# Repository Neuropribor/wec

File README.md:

# wec
An open-source Wireless Electrophysological Complex

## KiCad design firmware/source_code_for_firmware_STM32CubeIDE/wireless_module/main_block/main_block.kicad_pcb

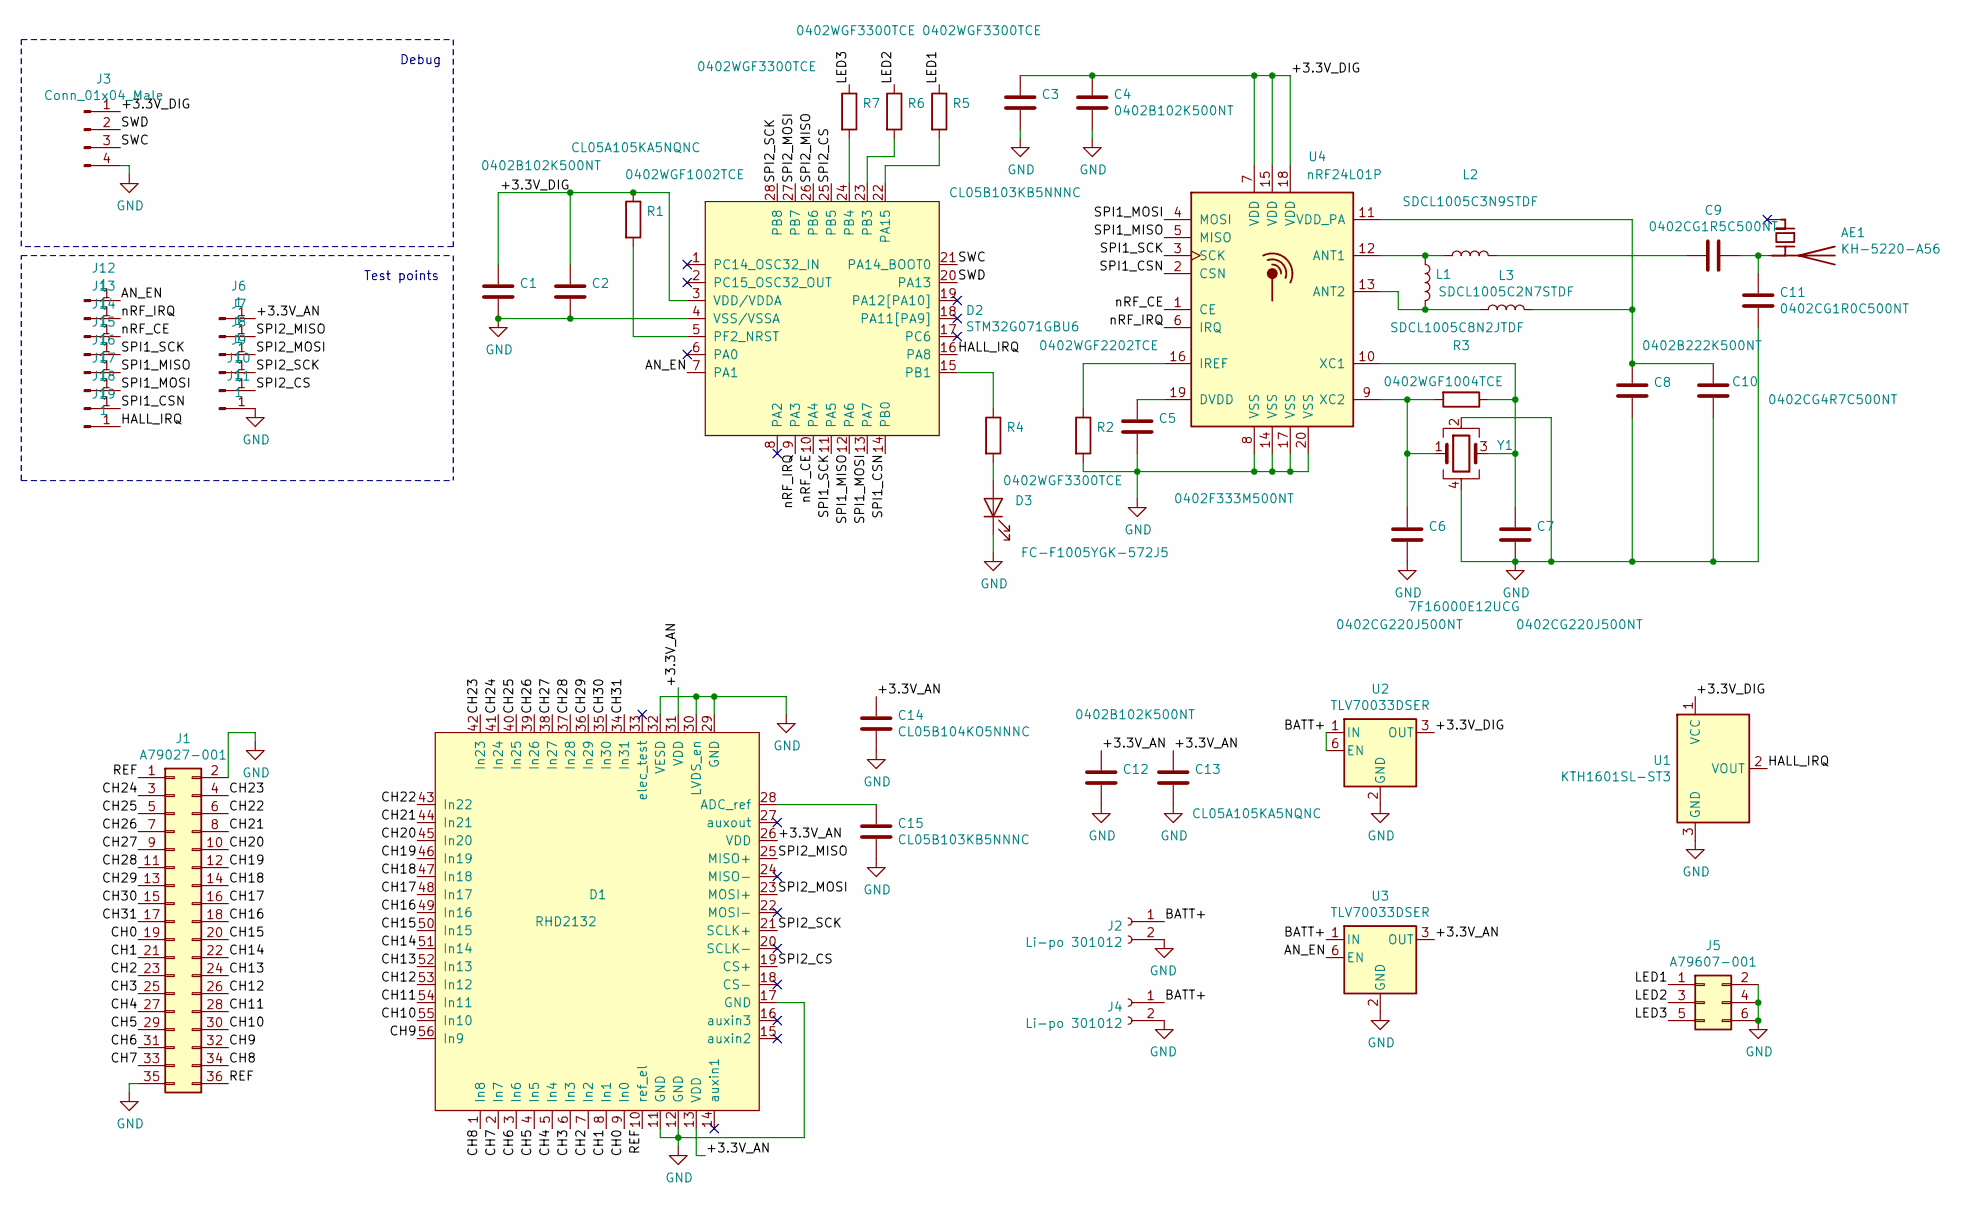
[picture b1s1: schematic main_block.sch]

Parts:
AE1: KH-5220-A56; R_2010_5025Metric_Pad1.52x2.65mm_HandSolder; LCSC C504003
C1, C4, C12: 0402B102K500NT; C_0402_1005Metric; LCSC C1523
C2, C13: CL05A105KA5NQNC; C_0402_1005Metric; LCSC C52923
C3, C15: CL05B103KB5NNNC; C_0402_1005Metric; LCSC C15195
C5: 0402F333M500NT; C_0402_1005Metric; LCSC C1585
C6, C7: 0402CG220J500NT; C_0402_1005Metric; LCSC C1555
C8: 0402B222K500NT; C_0402_1005Metric; LCSC C1531
C9: 0402CG1R5C500NT; C_0402_1005Metric; LCSC C1552
C10: 0402CG4R7C500NT; C_0402_1005Metric; LCSC C1569
C11: 0402CG1R0C500NT; C_0402_1005Metric; LCSC C1550
C14: CL05B104KO5NNNC; C_0402_1005Metric; LCSC C1525
D1: RHD2132; QFN-56-1EP_8x8mm_P0.5mm_EP4.5x5.2mm
D2: STM32G071GBU6; QFN50P400X400X60-28N; LCSC C529347
D3: FC-F1005YGK-572J5; LED_0402_1005Metric; LCSC C130722
J1: A79027-001
J2, J4: Li-po 301012; PinHeader_1x02_P2.00mm_Vertical
J3: Conn_01x04_Male; debug
J5: A79607-001
J6, J7, J8, J9, J10, J11, J12, J13, J14, J15, J16, J17, J18, J19: 1; debug_
L1: SDCL1005C8N2JTDF; L_0402_1005Metric; LCSC C16208
L2: SDCL1005C3N9STDF; L_0402_1005Metric; LCSC C14033
L3: SDCL1005C2N7STDF; L_0402_1005Metric; LCSC C27123
R1: 0402WGF1002TCE; R_0402_1005Metric; LCSC C25744
R2: 0402WGF2202TCE; R_0402_1005Metric; LCSC C25768
R3: 0402WGF1004TCE; R_0402_1005Metric; LCSC C26083
R4, R5, R6, R7: 0402WGF3300TCE; R_0402_1005Metric; LCSC C25104
U1: KTH1601SL-ST3; SOT-23; LCSC C516265
U2, U3: TLV70033DSER; WSON-6_1.5x1.5mm_P0.5mm; LCSC C97256
U4: nRF24L01P; QFN-20-1EP_4x4mm_P0.5mm_EP2.5x2.5mm; LCSC C8791
Y1: 7F16000E12UCG; Crystal_SMD_2016-4Pin_2.0x1.6mm; LCSC C252270

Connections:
/+3.3V_AN: C12.1, C13.1, C14.1, D1.13 (VDD), D1.26 (VDD), D1.31 (VDD), J6.1, U3.3 (OUT)
/+3.3V_DIG: C1.1, C2.1, C3.1, C4.1, D2.3 (VDD/VDDA), J3.1, R1.1, U1.1 (VCC), U2.3 (OUT), U4.7 (VDD), U4.15 (VDD), U4.18 (VDD)
/AN_EN: D2.7 (PA1), J12.1, U3.6 (EN)
/BATT+: J2.1, J4.1, U2.1 (IN), U2.6 (EN), U3.1 (IN)
/CH0: D1.9 (In0), J1.19
/CH1: D1.8 (In1), J1.21
/CH2: D1.7 (In2), J1.23
/CH3: D1.6 (In3), J1.25
/CH4: D1.5 (In4), J1.27
/CH5: D1.4 (In5), J1.29
/CH6: D1.3 (In6), J1.31
/CH7: D1.2 (In7), J1.33
/CH8: D1.1 (In8), J1.34
/CH9: D1.56 (In9), J1.32
/CH10: D1.55 (In10), J1.30
/CH11: D1.54 (In11), J1.28
/CH12: D1.53 (In12), J1.26
/CH13: D1.52 (In13), J1.24
/CH14: D1.51 (In14), J1.22
/CH15: D1.50 (In15), J1.20
/CH16: D1.49 (In16), J1.18
/CH17: D1.48 (In17), J1.16
/CH18: D1.47 (In18), J1.14
/CH19: D1.46 (In19), J1.12
/CH20: D1.45 (In20), J1.10
/CH21: D1.44 (In21), J1.8
/CH22: D1.43 (In22), J1.6
/CH23: D1.42 (In23), J1.4
/CH24: D1.41 (In24), J1.3
/CH25: D1.40 (In25), J1.5
/CH26: D1.39 (In26), J1.7
/CH27: D1.38 (In27), J1.9
/CH28: D1.37 (In28), J1.11
/CH29: D1.36 (In29), J1.13
/CH30: D1.35 (In30), J1.15
/CH31: D1.34 (In31), J1.17
/HALL_IRQ: D2.16 (PA8), J19.1, U1.2 (VOUT)
/LED1: J5.1, R5.1
/LED2: J5.3, R6.1
/LED3: J5.5, R7.1
/REF: D1.10 (ref_el), J1.1, J1.36
/SPI1_CSN: D2.14 (PB0), J18.1, U4.2 (CSN)
/SPI1_MISO: D2.12 (PA6), J16.1, U4.5 (MISO)
/SPI1_MOSI: D2.13 (PA7), J17.1, U4.4 (MOSI)
/SPI1_SCK: D2.11 (PA5), J15.1, U4.3 (SCK)
/SPI2_CS: D1.19 (CS+), D2.25 (PB5), J10.1
/SPI2_MISO: D1.25 (MISO+), D2.26 (PB6), J7.1
/SPI2_MOSI: D1.23 (MOSI+), D2.27 (PB7), J8.1
/SPI2_SCK: D1.21 (SCLK+), D2.28 (PB8), J9.1
/SWC: D2.21 (PA14_BOOT0), J3.3
/SWD: D2.20 (PA13), J3.2
/nRF_CE: D2.10 (PA4), J14.1, U4.1 (CE)
/nRF_IRQ: D2.9 (PA3), J13.1, U4.6 (IRQ)
GND: C1.2, C2.2, C3.2, C4.2, C5.2, C6.2, C7.2, C8.2, C10.2, C11.2, C12.2, C13.2, C14.2, C15.2, D1.11 (GND), D1.12 (GND), D1.17 (GND), D1.29 (GND), D1.30 (LVDS_en), D1.32 (VESD), D2.4 (VSS/VSSA), D3.1 (K), J1.2, J1.35, J2.2, J3.4, J4.2, J5.2, J5.4, J5.6, J11.1, R2.2, U1.3 (GND), U2.2 (GND), U3.2 (GND), U4.8 (VSS), U4.14 (VSS), U4.17 (VSS), U4.20 (VSS), Y1.2, Y1.4
unnamed: AE1.2 (PCB_Trace), C9.1, C11.1
unnamed: C5.1, U4.19 (DVDD)
unnamed: C6.1, R3.2, U4.9 (XC2), Y1.1
unnamed: C7.1, R3.1, U4.10 (XC1), Y1.3
unnamed: C9.2, L2.2
unnamed: C8.1, C10.1, L3.2, U4.11 (VDD_PA)
unnamed: C15.1, D1.28 (ADC_ref)
unnamed: D2.5 (PF2_NRST), R1.2
unnamed: D2.15 (PB1), R4.1
unnamed: D2.22 (PA15), R5.2
unnamed: D2.23 (PB3), R6.2
unnamed: D2.24 (PB4), R7.2
unnamed: D3.2 (A), R4.2
unnamed: L1.1, L2.1, U4.12 (ANT1)
unnamed: L1.2, L3.1, U4.13 (ANT2)
unnamed: R2.1, U4.16 (IREF)

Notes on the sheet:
Test points
Debug

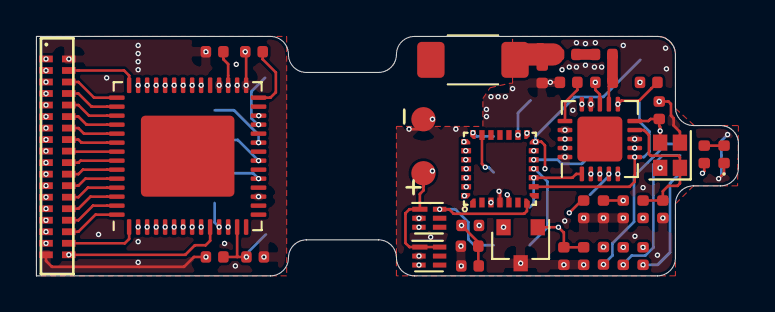
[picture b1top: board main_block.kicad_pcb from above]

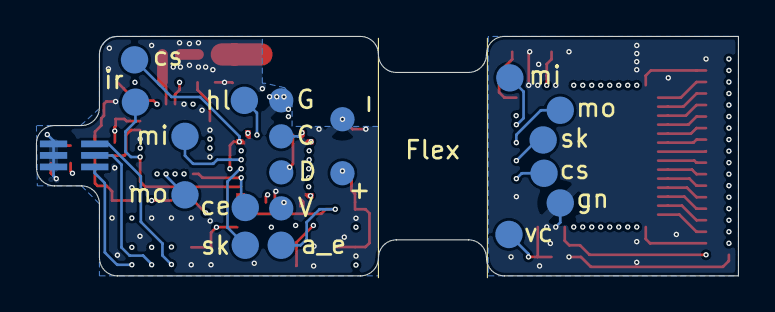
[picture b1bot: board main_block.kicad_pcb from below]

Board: 4 copper layers, 39.0 x 13.3 mm, 53 parts (17 on the bottom side), 70 nets.

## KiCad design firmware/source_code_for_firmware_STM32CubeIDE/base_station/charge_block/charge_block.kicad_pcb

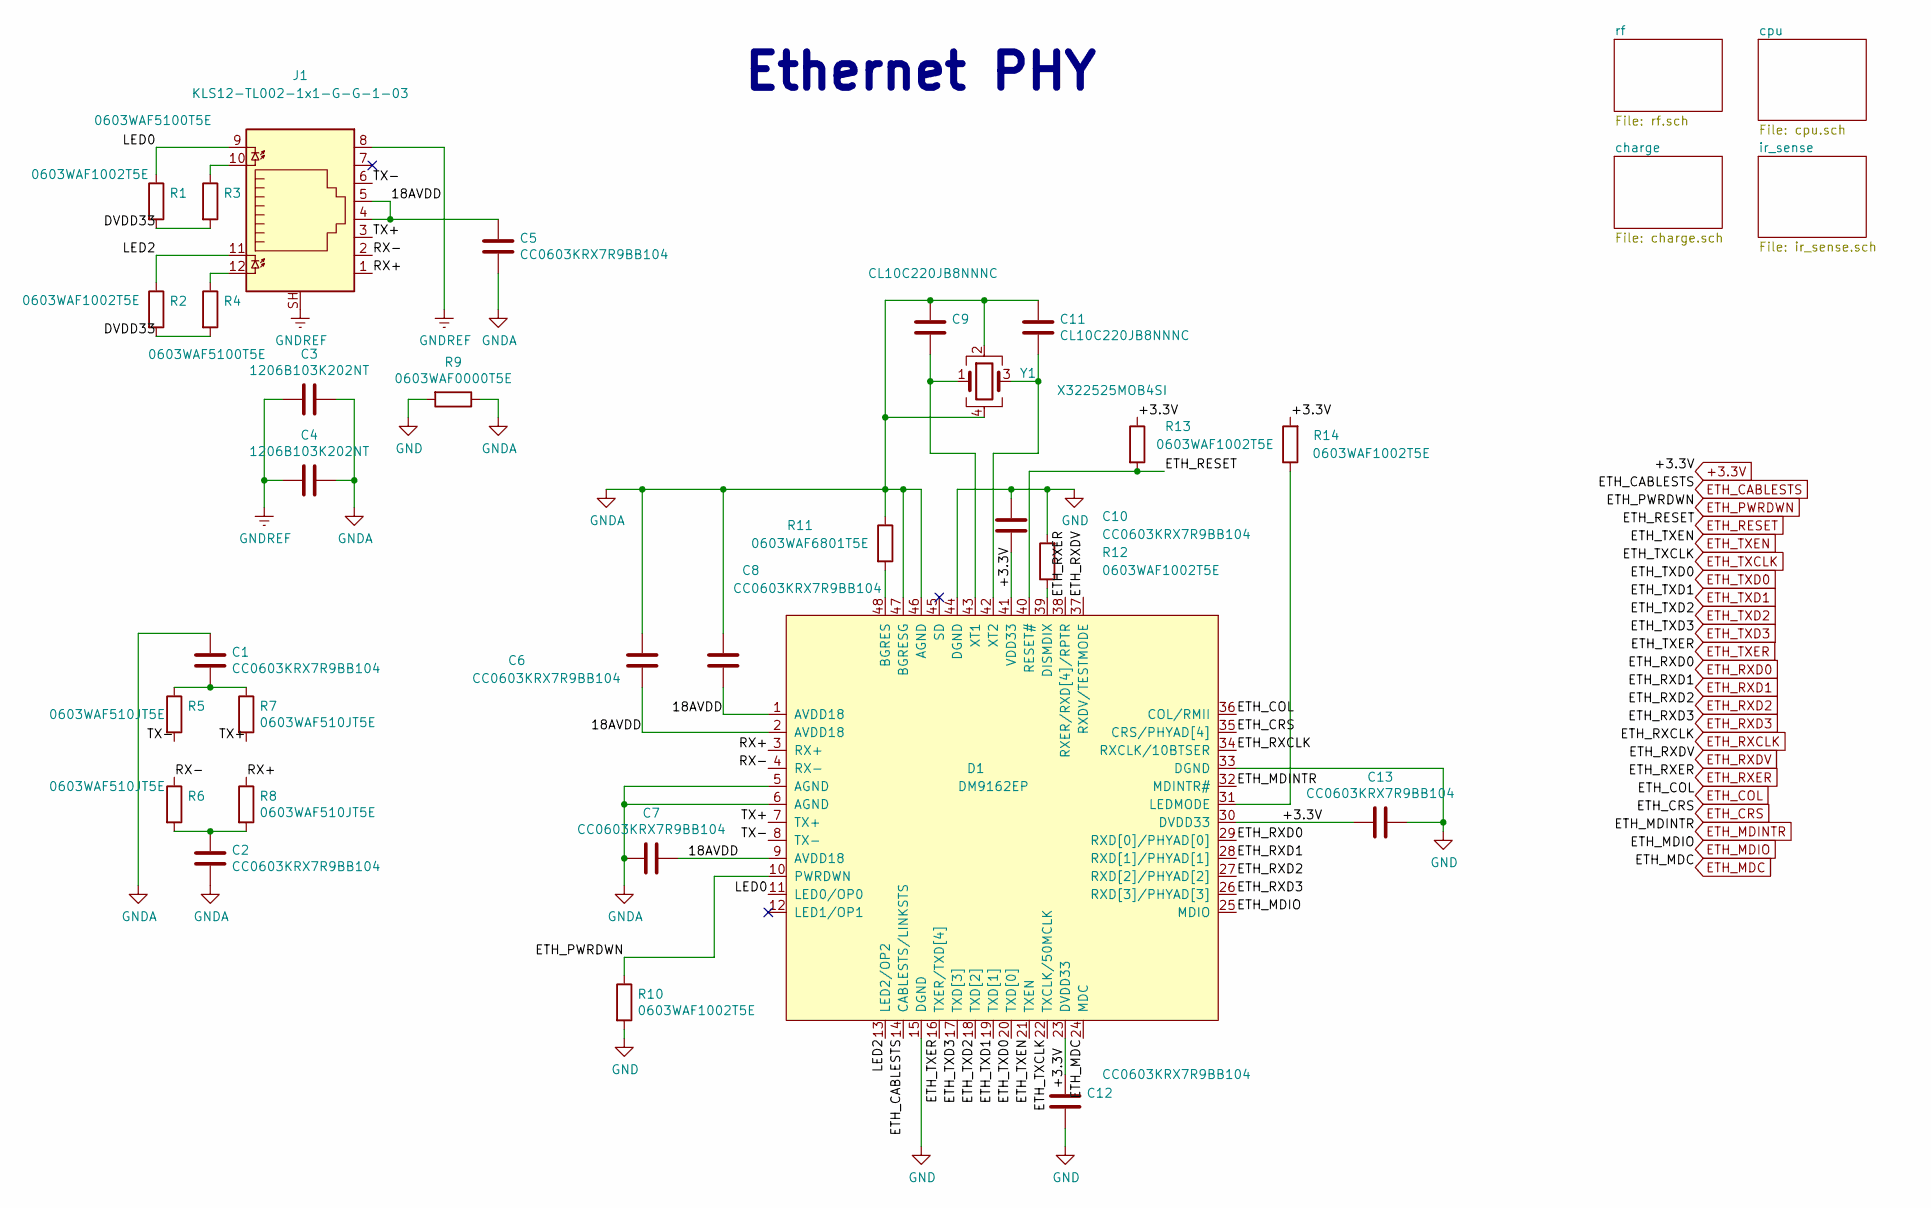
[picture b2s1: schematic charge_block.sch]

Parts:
C1, C2, C5, C6, C7, C8, C10, C12, C13: CC0603KRX7R9BB104; C_0603_1608Metric; LCSC C14663
C3, C4: 1206B103K202NT; C_1206_3216Metric; LCSC C53737
C9, C11: CL10C220JB8NNNC; C_0603_1608Metric; LCSC C1653
D1: DM9162EP; LQFP-48_7x7mm_P0.5mm; LCSC C692729
J1: KLS12-TL002-1x1-G-G-1-03; KLS12-TL002
R1, R2, R10, R12, R13, R14: 0603WAF1002T5E; R_0603_1608Metric; LCSC C25804
R3, R4: 0603WAF5100T5E; R_0603_1608Metric; LCSC C23193
R5, R6, R7, R8: 0603WAF510JT5E; R_0603_1608Metric; LCSC C23197
R9: 0603WAF0000T5E; R_0603_1608Metric; LCSC C21189
R11: 0603WAF6801T5E; R_0603_1608Metric; LCSC C23212
Y1: X322525MOB4SI; Crystal_SMD_3225-4Pin_3.2x2.5mm; LCSC C9006

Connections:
+3.3V: C10.2, C12.2, C13.1, D1.23 (DVDD33), D1.30 (DVDD33), D1.41 (VDD33), R13.1, R14.2; also elsewhere on the board
/18AVDD: C5.1, C6.2, C7.1, C8.2, D1.1 (AVDD18), D1.2 (AVDD18), D1.9 (AVDD18), J1.4, J1.5
/DVDD33: R1.2, R2.2, R3.2, R4.2
/LED0: D1.11 (LED0/OP0), J1.9, R1.1
/LED2: D1.13 (LED2/OP2), J1.11, R2.1
/RX+: D1.3 (RX+), J1.1, R8.1
/RX-: D1.4 (RX-), J1.2, R6.1
/TX+: D1.7 (TX+), J1.3, R7.2
/TX-: D1.8 (TX-), J1.6, R5.2
ETH_CABLESTS: D1.14 (CABLESTS/LINKSTS); also elsewhere on the board
ETH_COL: D1.36 (COL/RMII); also elsewhere on the board
ETH_CRS: D1.35 (CRS/PHYAD[4]); also elsewhere on the board
ETH_MDC: D1.24 (MDC); also elsewhere on the board
ETH_MDINTR: D1.32 (MDINTR#); also elsewhere on the board
ETH_MDIO: D1.25 (MDIO); also elsewhere on the board
ETH_PWRDWN: D1.10 (PWRDWN), R10.1; also elsewhere on the board
ETH_RESET: D1.40 (RESET#), R13.2; also elsewhere on the board
ETH_RXCLK: D1.34 (RXCLK/10BTSER); also elsewhere on the board
ETH_RXD0: D1.29 (RXD[0]/PHYAD[0]); also elsewhere on the board
ETH_RXD1: D1.28 (RXD[1]/PHYAD[1]); also elsewhere on the board
ETH_RXD2: D1.27 (RXD[2]/PHYAD[2]); also elsewhere on the board
ETH_RXD3: D1.26 (RXD[3]/PHYAD[3]); also elsewhere on the board
ETH_RXDV: D1.37 (RXDV/TESTMODE); also elsewhere on the board
ETH_RXER: D1.38 (RXER/RXD[4]/RPTR); also elsewhere on the board
ETH_TXCLK: D1.22 (TXCLK/50MCLK); also elsewhere on the board
ETH_TXD0: D1.20 (TXD[0]); also elsewhere on the board
ETH_TXD1: D1.19 (TXD[1]); also elsewhere on the board
ETH_TXD2: D1.18 (TXD[2]); also elsewhere on the board
ETH_TXD3: D1.17 (TXD[3]); also elsewhere on the board
ETH_TXEN: D1.21 (TXEN); also elsewhere on the board
ETH_TXER: D1.16 (TXER/TXD[4])
GND: C10.1, C12.1, C13.2, D1.15 (DGND), D1.33 (DGND), D1.44 (DGND), R9.2, R10.2, R12.2; also elsewhere on the board
GNDA: C1.1, C2.2, C3.1, C4.1, C5.2, C6.1, C7.2, C8.1, C9.1, C11.1, D1.5 (AGND), D1.6 (AGND), D1.46 (AGND), D1.47 (BGRESG), R9.1, R11.1, Y1.2, Y1.4
GNDREF: C3.2, C4.2, J1.8, J1.SH; also elsewhere on the board
unnamed: C1.2, R5.1, R7.1
unnamed: C2.1, R6.2, R8.2
unnamed: C9.2, D1.43 (XT1), Y1.1
unnamed: C11.2, D1.42 (XT2), Y1.3
unnamed: D1.31 (LEDMODE), R14.1
unnamed: D1.39 (DISMDIX), R12.1
unnamed: D1.48 (BGRES), R11.2
unnamed: J1.10, R3.1
unnamed: J1.12, R4.1

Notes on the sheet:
Ethernet PHY

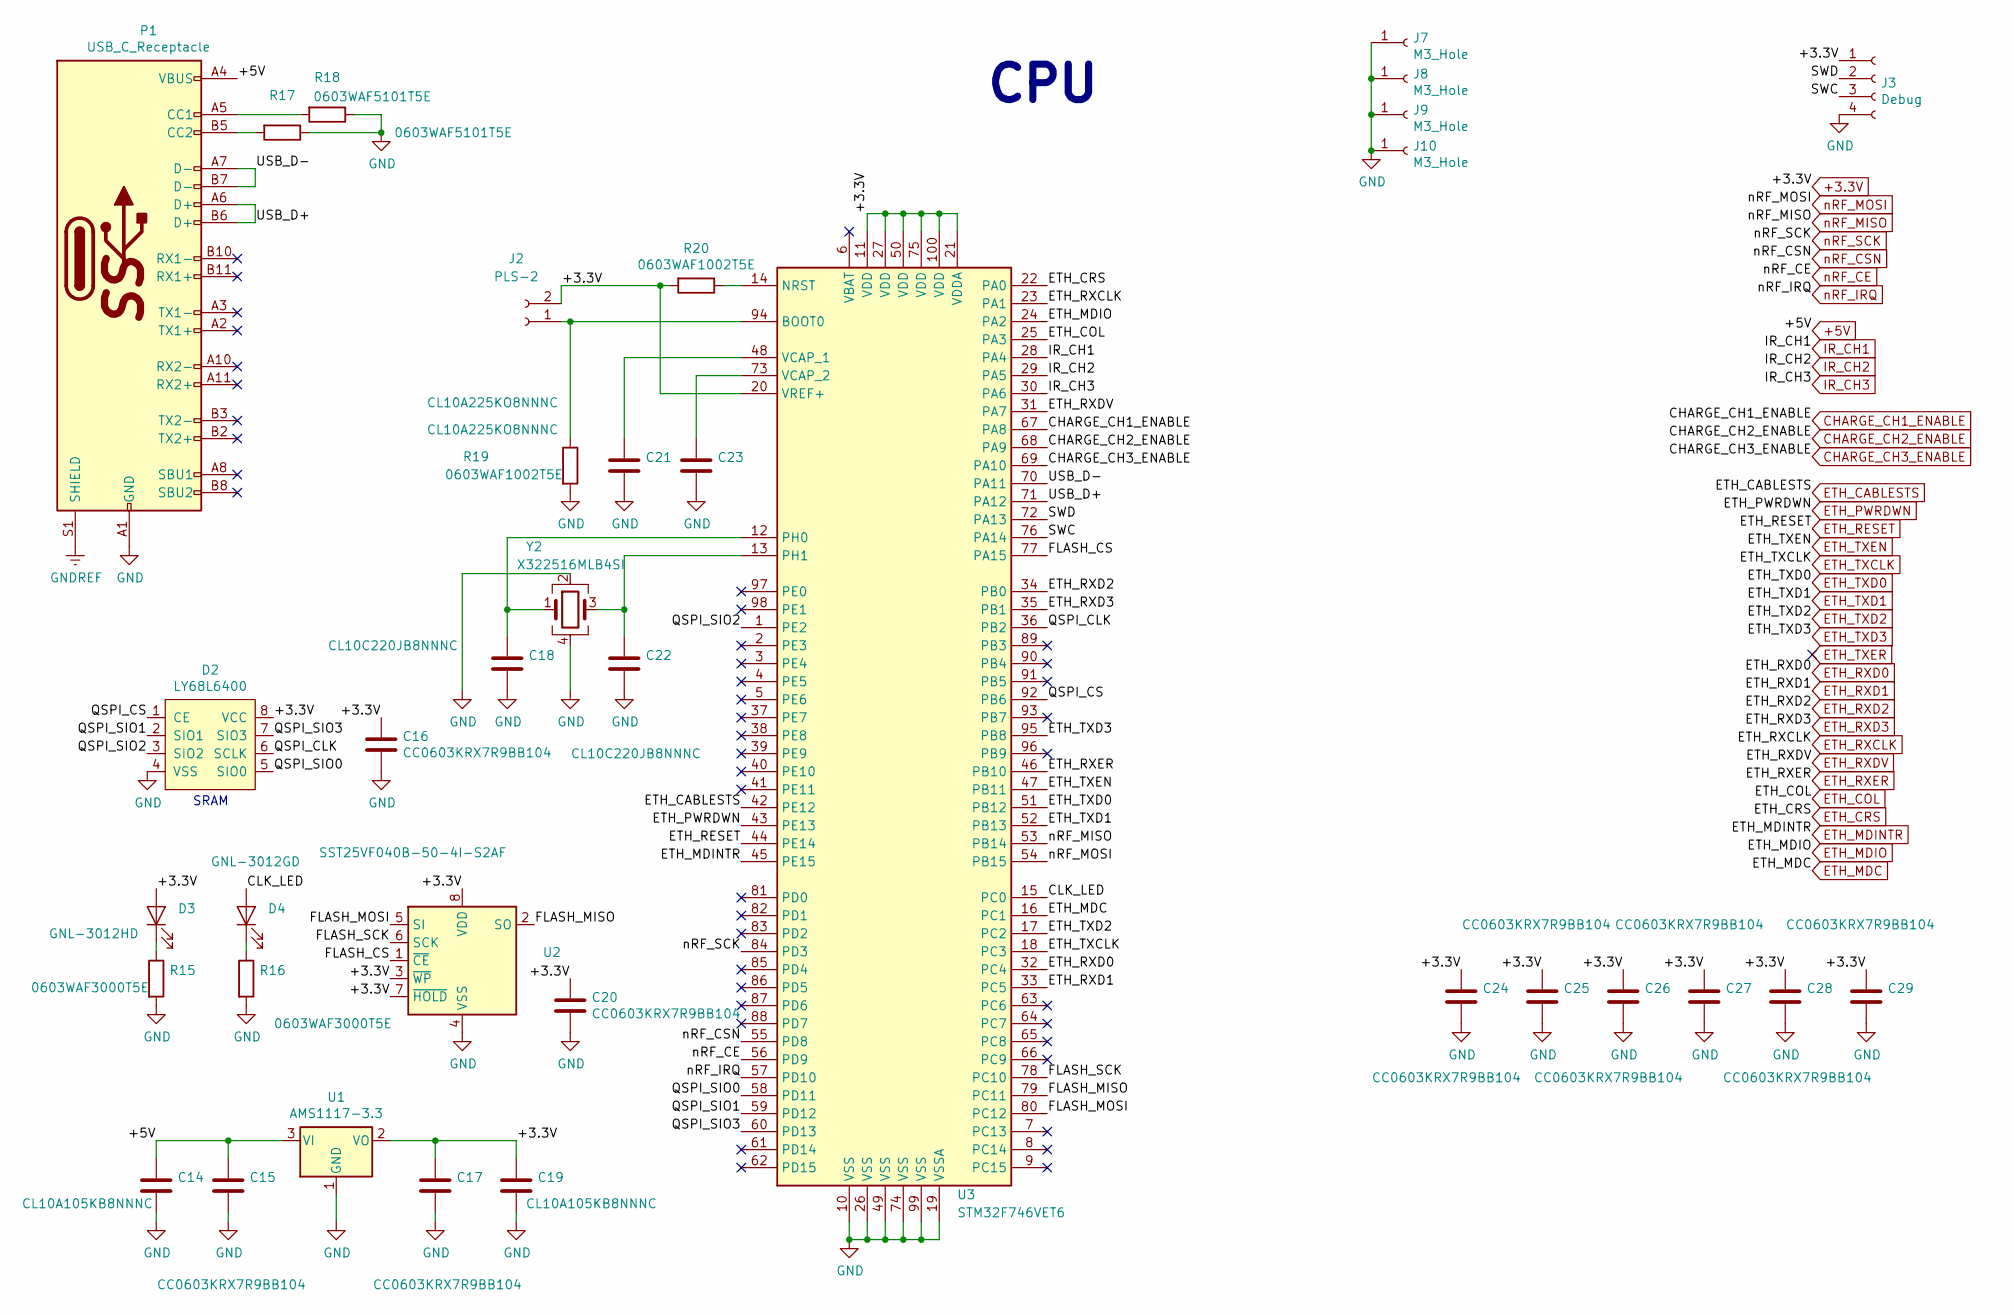
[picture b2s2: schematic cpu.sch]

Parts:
C14, C19: CL10A105KB8NNNC; C_0603_1608Metric; LCSC C15849
C15, C16, C17, C20, C24, C25, C26, C27, C28, C29: CC0603KRX7R9BB104; C_0603_1608Metric; LCSC C14663
C18, C22: CL10C220JB8NNNC; C_0603_1608Metric; LCSC C1653
C21, C23: CL10A225KO8NNNC; C_0603_1608Metric; LCSC C23630
D2: LY68L6400; SO-8_3.9x4.9mm_P1.27mm; LCSC C261881
D3: GNL-3012HD; LED_D3.0mm
D4: GNL-3012GD; LED_D3.0mm
J2: PLS-2; PinHeader_1x02_P2.54mm_Vertical
J3: Debug; PinHeader_1x04_P2.54mm_Vertical
J7, J8, J9, J10: M3_Hole; MountingHole_3.2mm_M3
P1: USB_C_Receptacle; USB_C_16_pin
R15, R16: 0603WAF3000T5E; R_0603_1608Metric; LCSC C23025
R17, R18: 0603WAF5101T5E; R_0603_1608Metric; LCSC C23186
R19, R20: 0603WAF1002T5E; R_0603_1608Metric; LCSC C25804
U1: AMS1117-3.3; SOT-223-3_TabPin2; LCSC C6186
U2: SST25VF040B-50-4I-S2AF; SOIC-8_5.275x5.275mm_P1.27mm; LCSC C178274
U3: STM32F746VET6; LQFP-100_14x14mm_P0.5mm; LCSC C117505
Y2: X322516MLB4SI; Crystal_SMD_3225-4Pin_3.2x2.5mm; LCSC C13738

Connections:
+3.3V: C16.1, C17.1, C19.1, C20.1, C24.1, C25.1, C26.1, C27.1, C28.1, C29.1, D2.8 (VCC), D3.2 (A), J2.2, J3.1, R20.2, U1.2 (VO), U2.3 (~WP~), U2.7 (~HOLD~), U2.8 (VDD), U3.11 (VDD), U3.20 (VREF+), U3.21 (VDDA), U3.27 (VDD), U3.50 (VDD), U3.75 (VDD), U3.100 (VDD); also elsewhere on the board
+5V: C14.1, C15.1, P1.A4 (VBUS), P1.A9 (VBUS), P1.B4 (VBUS), P1.B9 (VBUS), U1.3 (VI); also elsewhere on the board
/cpu/CLK_LED: D4.2 (A), U3.15 (PC0)
/cpu/FLASH_CS: U2.1 (~CE), U3.77 (PA15)
/cpu/FLASH_MISO: U2.2 (SO), U3.79 (PC11)
/cpu/FLASH_MOSI: U2.5 (SI), U3.80 (PC12)
/cpu/FLASH_SCK: U2.6 (SCK), U3.78 (PC10)
/cpu/QSPI_CLK: D2.6 (SCLK), U3.36 (PB2)
/cpu/QSPI_CS: D2.1 (CE), U3.92 (PB6)
/cpu/QSPI_SIO0: D2.5 (SIO0), U3.58 (PD11)
/cpu/QSPI_SIO1: D2.2 (SIO1), U3.59 (PD12)
/cpu/QSPI_SIO2: D2.3 (SIO2), U3.1 (PE2)
/cpu/QSPI_SIO3: D2.7 (SIO3), U3.60 (PD13)
/cpu/SWC: J3.3, U3.76 (PA14)
/cpu/SWD: J3.2, U3.72 (PA13)
/cpu/USB_D+: P1.A6 (D+), P1.B6 (D+), U3.71 (PA12)
/cpu/USB_D-: P1.A7 (D-), P1.B7 (D-), U3.70 (PA11)
CHARGE_CH1_ENABLE: U3.67 (PA8); also elsewhere on the board
CHARGE_CH2_ENABLE: U3.68 (PA9); also elsewhere on the board
CHARGE_CH3_ENABLE: U3.69 (PA10); also elsewhere on the board
ETH_CABLESTS: U3.42 (PE12); also elsewhere on the board
ETH_COL: U3.25 (PA3); also elsewhere on the board
ETH_CRS: U3.22 (PA0); also elsewhere on the board
ETH_MDC: U3.16 (PC1); also elsewhere on the board
ETH_MDINTR: U3.45 (PE15); also elsewhere on the board
ETH_MDIO: U3.24 (PA2); also elsewhere on the board
ETH_PWRDWN: U3.43 (PE13); also elsewhere on the board
ETH_RESET: U3.44 (PE14); also elsewhere on the board
ETH_RXCLK: U3.23 (PA1); also elsewhere on the board
ETH_RXD0: U3.32 (PC4); also elsewhere on the board
ETH_RXD1: U3.33 (PC5); also elsewhere on the board
ETH_RXD2: U3.34 (PB0); also elsewhere on the board
ETH_RXD3: U3.35 (PB1); also elsewhere on the board
ETH_RXDV: U3.31 (PA7); also elsewhere on the board
ETH_RXER: U3.46 (PB10); also elsewhere on the board
ETH_TXCLK: U3.18 (PC3); also elsewhere on the board
ETH_TXD0: U3.51 (PB12); also elsewhere on the board
ETH_TXD1: U3.52 (PB13); also elsewhere on the board
ETH_TXD2: U3.17 (PC2); also elsewhere on the board
ETH_TXD3: U3.95 (PB8); also elsewhere on the board
ETH_TXEN: U3.47 (PB11); also elsewhere on the board
GND: C14.2, C15.2, C16.2, C17.2, C18.2, C19.2, C20.2, C21.2, C22.2, C23.2, C24.2, C25.2, C26.2, C27.2, C28.2, C29.2, D2.4 (VSS), J3.4, J7.1, J8.1, J9.1, J10.1, P1.A1 (GND), P1.A12 (GND), P1.B1 (GND), P1.B12 (GND), R15.2, R16.2, R17.1, R18.1, R19.2, U1.1 (GND), U2.4 (VSS), U3.10 (VSS), U3.19 (VSSA), U3.26 (VSS), U3.49 (VSS), U3.74 (VSS), U3.99 (VSS), Y2.2, Y2.4; also elsewhere on the board
GNDREF: P1.S1 (SHIELD); also elsewhere on the board
IR_CH1: U3.28 (PA4); also elsewhere on the board
IR_CH2: U3.29 (PA5); also elsewhere on the board
IR_CH3: U3.30 (PA6); also elsewhere on the board
unnamed: C18.1, U3.12 (PH0), Y2.1
unnamed: C21.1, U3.48 (VCAP_1)
unnamed: C22.1, U3.13 (PH1), Y2.3
unnamed: C23.1, U3.73 (VCAP_2)
unnamed: D3.1 (K), R15.1
unnamed: D4.1 (K), R16.1
unnamed: J2.1, R19.1, U3.94 (BOOT0)
unnamed: P1.A5 (CC1), R18.2
unnamed: P1.B5 (CC2), R17.2
unnamed: R20.1, U3.14 (NRST)
nRF_CE: U3.56 (PD9); also elsewhere on the board
nRF_CSN: U3.55 (PD8); also elsewhere on the board
nRF_IRQ: U3.57 (PD10); also elsewhere on the board
nRF_MISO: U3.53 (PB14); also elsewhere on the board
nRF_MOSI: U3.54 (PB15); also elsewhere on the board
nRF_SCK: U3.84 (PD3); also elsewhere on the board

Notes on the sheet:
SRAM
CPU

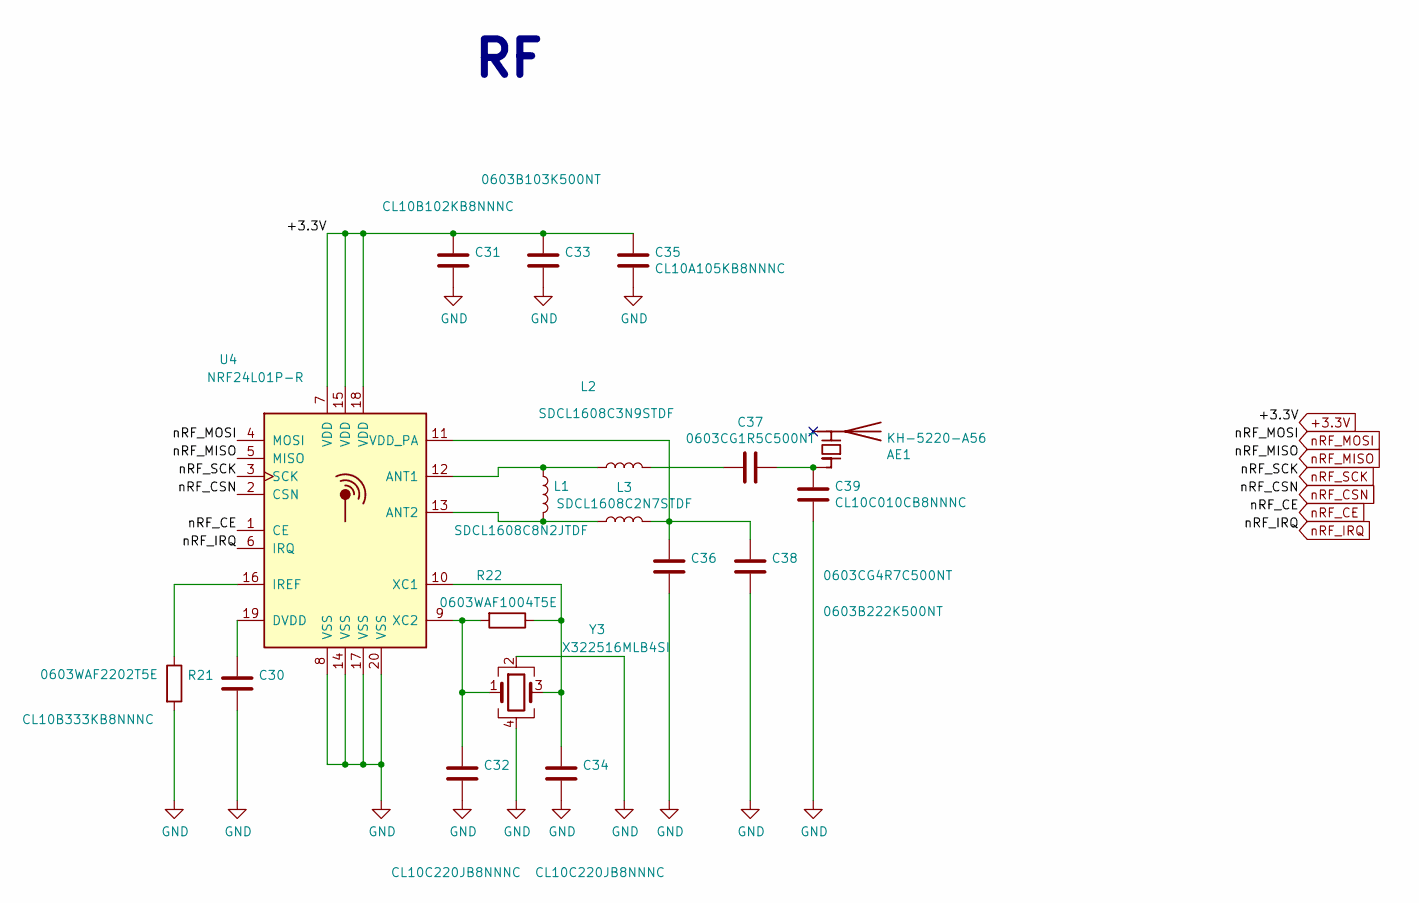
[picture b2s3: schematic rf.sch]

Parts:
AE1: KH-5220-A56; LCSC C504003
C30: CL10B333KB8NNNC; C_0603_1608Metric; LCSC C21117
C31: CL10B102KB8NNNC; C_0603_1608Metric; LCSC C1588
C32, C34: CL10C220JB8NNNC; C_0603_1608Metric; LCSC C1653
C33: 0603B103K500NT; C_0603_1608Metric; LCSC C57112
C35: CL10A105KB8NNNC; C_0603_1608Metric; LCSC C15849
C36: 0603B222K500NT; C_0603_1608Metric; LCSC C1604
C37: 0603CG1R5C500NT; C_0603_1608Metric; LCSC C1639
C38: 0603CG4R7C500NT; C_0603_1608Metric; LCSC C1669
C39: CL10C010CB8NNNC; C_0603_1608Metric; LCSC C23969
L1: SDCL1608C8N2JTDF; L_0603_1608Metric; LCSC C1032
L2: SDCL1608C3N9STDF; L_0603_1608Metric; LCSC C13818
L3: SDCL1608C2N7STDF; L_0603_1608Metric; LCSC C13817
R21: 0603WAF2202T5E; R_0603_1608Metric; LCSC C31850
R22: 0603WAF1004T5E; R_0603_1608Metric; LCSC C22935
U4: NRF24L01P-R; QFN-20-1EP_4x4mm_P0.5mm_EP2.5x2.5mm; LCSC C8791
Y3: X322516MLB4SI; Crystal_SMD_3225-4Pin_3.2x2.5mm; LCSC C13738

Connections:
+3.3V: C31.1, C33.1, C35.1, U4.7 (VDD), U4.15 (VDD), U4.18 (VDD); also elsewhere on the board
GND: C30.1, C31.2, C32.2, C33.2, C34.2, C35.2, C36.1, C38.1, C39.1, R21.2, U4.8 (VSS), U4.14 (VSS), U4.17 (VSS), U4.20 (VSS), Y3.2, Y3.4; also elsewhere on the board
unnamed: AE1.1 (FEED), C37.1, C39.2
unnamed: C30.2, U4.19 (DVDD)
unnamed: C32.1, R22.2, U4.9 (XC2), Y3.1
unnamed: C34.1, R22.1, U4.10 (XC1), Y3.3
unnamed: C36.2, C38.2, L3.2, U4.11 (VDD_PA)
unnamed: C37.2, L2.2
unnamed: L1.1, L2.1, U4.12 (ANT1)
unnamed: L1.2, L3.1, U4.13 (ANT2)
unnamed: R21.1, U4.16 (IREF)
nRF_CE: U4.1 (CE); also elsewhere on the board
nRF_CSN: U4.2 (CSN); also elsewhere on the board
nRF_IRQ: U4.6 (IRQ); also elsewhere on the board
nRF_MISO: U4.5 (MISO); also elsewhere on the board
nRF_MOSI: U4.4 (MOSI); also elsewhere on the board
nRF_SCK: U4.3 (SCK); also elsewhere on the board

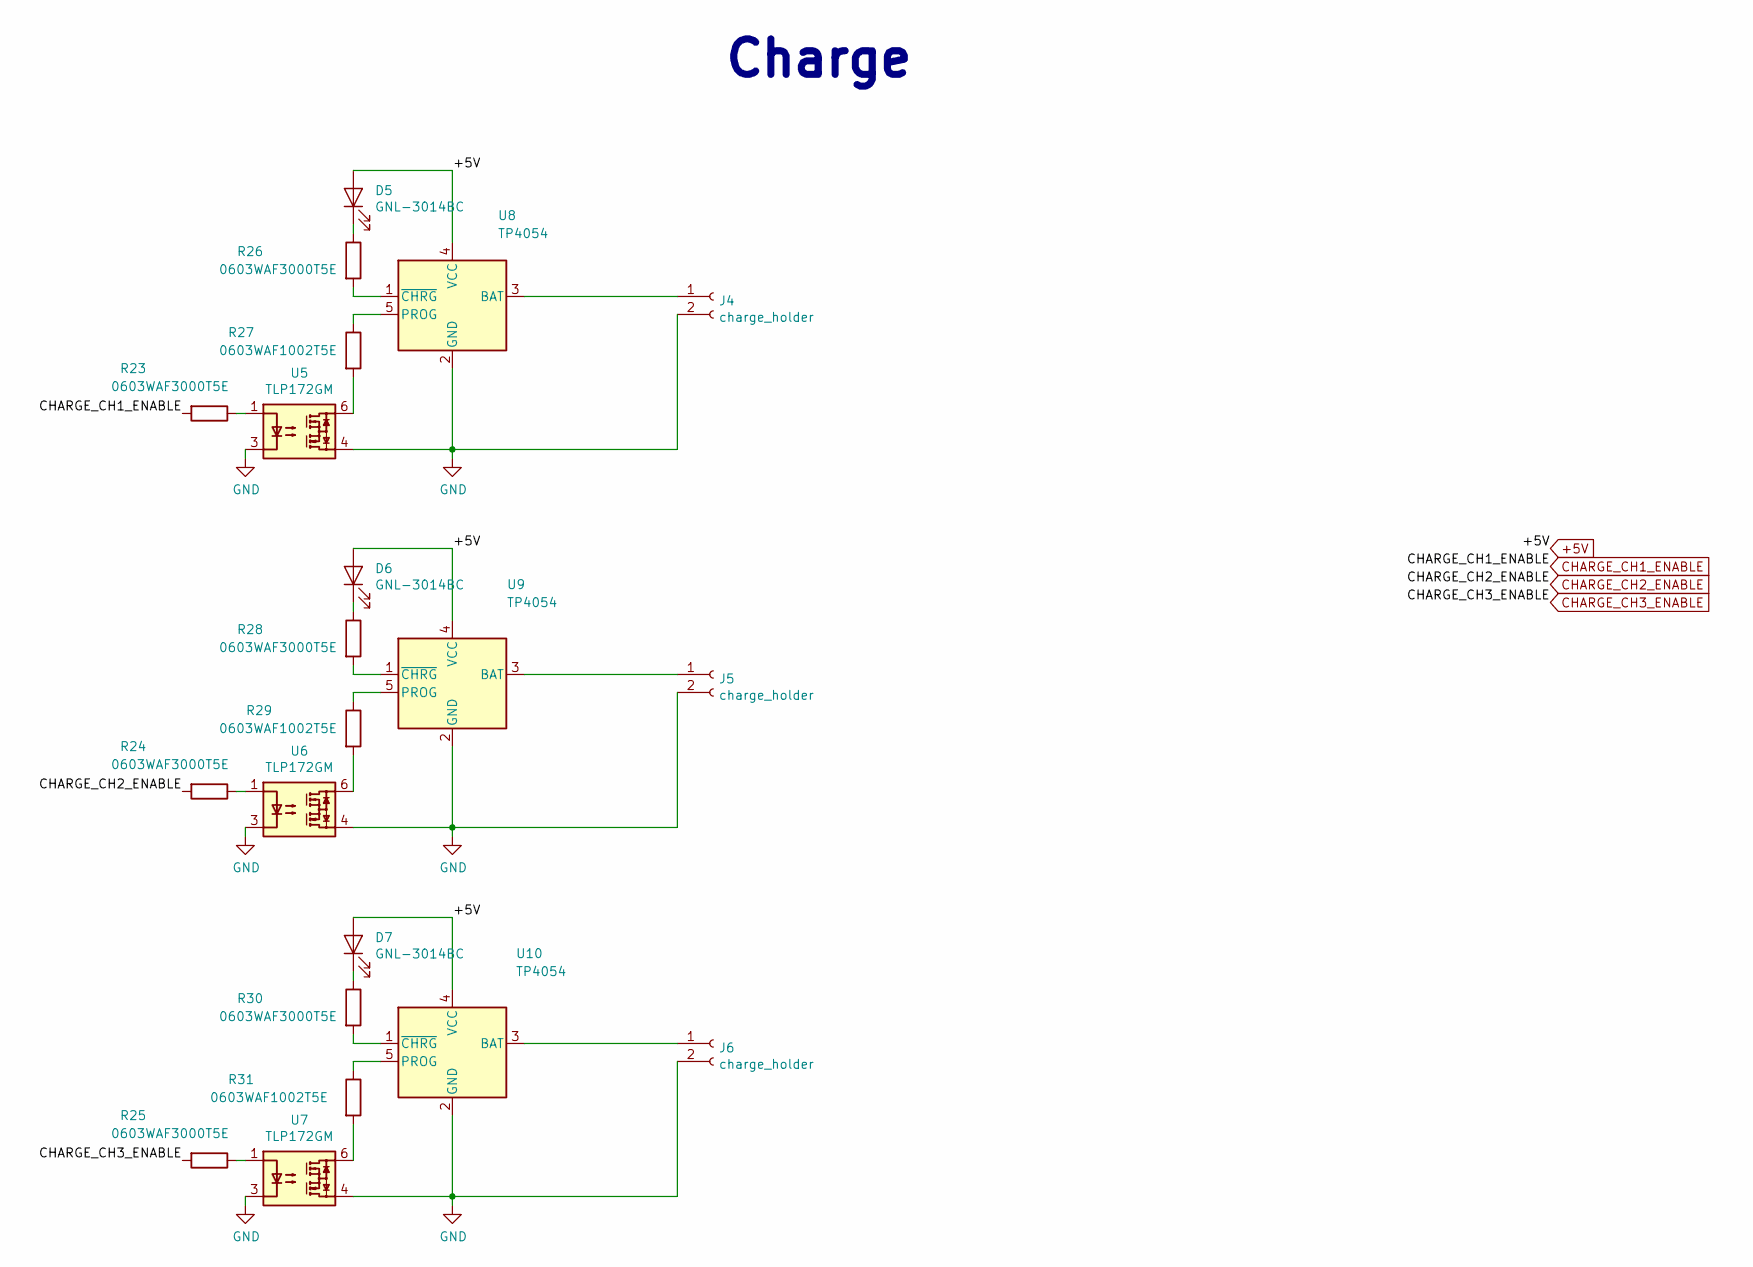
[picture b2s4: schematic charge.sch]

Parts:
D5, D6, D7: GNL-3014BC; LED_D3.0mm
J4, J5, J6: charge_holder; holder
R23, R24, R25, R26, R28, R30: 0603WAF3000T5E; R_0603_1608Metric; LCSC C23025
R27, R29, R31: 0603WAF1002T5E; R_0603_1608Metric; LCSC C25804
U5, U6, U7: TLP172GM; MFSOP6-4_4.4x3.6mm_P1.27mm; LCSC C261926
U8, U9, U10: TP4054; TSOT-23-5; LCSC C32574

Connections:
+5V: D5.2 (A), D6.2 (A), D7.2 (A), U8.4 (VCC), U9.4 (VCC), U10.4 (VCC); also elsewhere on the board
CHARGE_CH1_ENABLE: R23.2; also elsewhere on the board
CHARGE_CH2_ENABLE: R24.2; also elsewhere on the board
CHARGE_CH3_ENABLE: R25.2; also elsewhere on the board
GND: J4.2, J5.2, J6.2, U5.3, U5.4, U6.3, U6.4, U7.3, U7.4, U8.2 (GND), U9.2 (GND), U10.2 (GND); also elsewhere on the board
unnamed: D5.1 (K), R26.1
unnamed: D6.1 (K), R28.1
unnamed: D7.1 (K), R30.1
unnamed: J4.1, U8.3 (BAT)
unnamed: J5.1, U9.3 (BAT)
unnamed: J6.1, U10.3 (BAT)
unnamed: R23.1, U5.1
unnamed: R24.1, U6.1
unnamed: R25.1, U7.1
unnamed: R26.2, U8.1 (~CHRG)
unnamed: R27.1, U8.5 (PROG)
unnamed: R27.2, U5.6
unnamed: R28.2, U9.1 (~CHRG)
unnamed: R29.1, U9.5 (PROG)
unnamed: R29.2, U6.6
unnamed: R30.2, U10.1 (~CHRG)
unnamed: R31.1, U10.5 (PROG)
unnamed: R31.2, U7.6

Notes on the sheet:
Charge

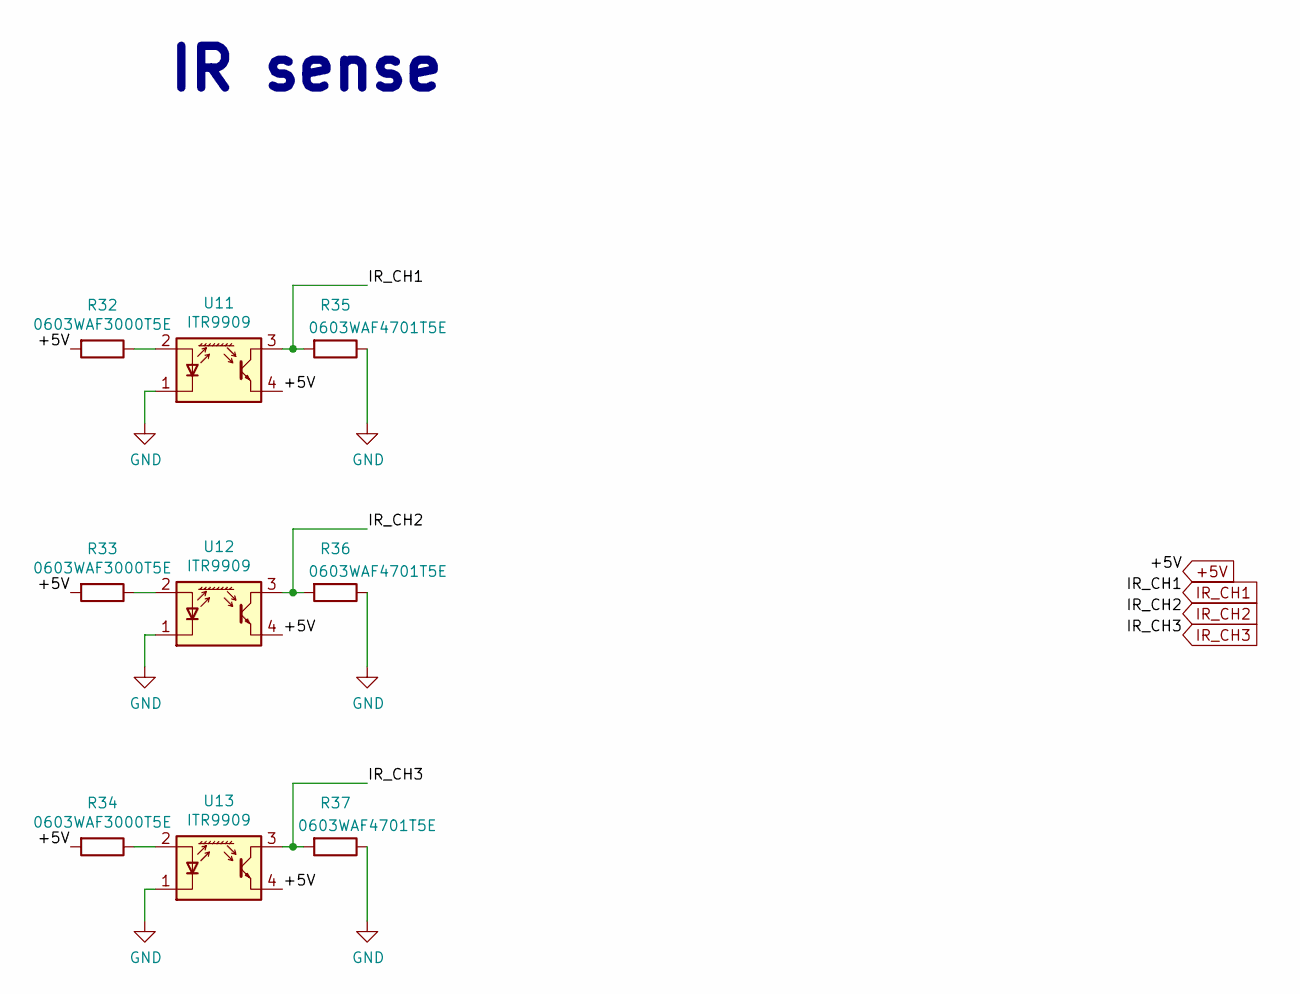
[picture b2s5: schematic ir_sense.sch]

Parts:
R32, R33, R34: 0603WAF3000T5E; R_0603_1608Metric; LCSC C23025
R35, R36, R37: 0603WAF4701T5E; R_0603_1608Metric; LCSC C23162
U11, U12, U13: ITR9909; ITR9909_ang

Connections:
+5V: R32.2, R33.2, R34.2, U11.4 (E), U12.4 (E), U13.4 (E); also elsewhere on the board
GND: R35.1, R36.1, R37.1, U11.1 (K), U12.1 (K), U13.1 (K); also elsewhere on the board
IR_CH1: R35.2, U11.3 (C); also elsewhere on the board
IR_CH2: R36.2, U12.3 (C); also elsewhere on the board
IR_CH3: R37.2, U13.3 (C); also elsewhere on the board
unnamed: R32.1, U11.2 (A)
unnamed: R33.1, U12.2 (A)
unnamed: R34.1, U13.2 (A)

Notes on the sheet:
IR sense
